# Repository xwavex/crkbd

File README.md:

# Singularity Keyboard, based on the Corne Keyboard.

## Parts
| Part | Amount | Description |
|:-|:-|:-|
| PCB | 2 | |
| Plate | 2 | |
| ProMicro | 2 | https://www.makershop.de/plattformen/arduino/pro-micro-32u4/ |
| TRRS Jack | 2 | MJ-4PP-9, PJ320A (3.5mm jack) |
| TRS(3-Pol) Cable | 1 | TRRS(4-Pol) Cable may be used as well? |
| Tactile Reset Switch | 2 | |
| Diode 1n4148w (sod 123) | 56 | For Low-Pro only surface mountable |
| Keyswitch | 56 | |
| Keycap | 56 | 54 x 1u and 2 x 1.5u |
| Standoffs / Spacer M2 | 14 | 6 mm for High-Pro, 4mm for Low-Pro |
| Standoffs / Spacer M2 8 mm or 10 mm | 4 | For OLED height |
| Screws M2 | 36 | 3 mm and 5 mm ? |
| Rubber feets | 8-10 | |

| Part (optional) | Amount | Description |
|:-|:-|:-|
| OLED Display | 2 | |
| 4 Pin Header | 2 | For easier exchange of OLED |
| 4 Pin  Sockets | 2 | For easier exchange of OLED |
| SK6812MINI | 72 | Top-facing 28, Bottom-facing 8 |

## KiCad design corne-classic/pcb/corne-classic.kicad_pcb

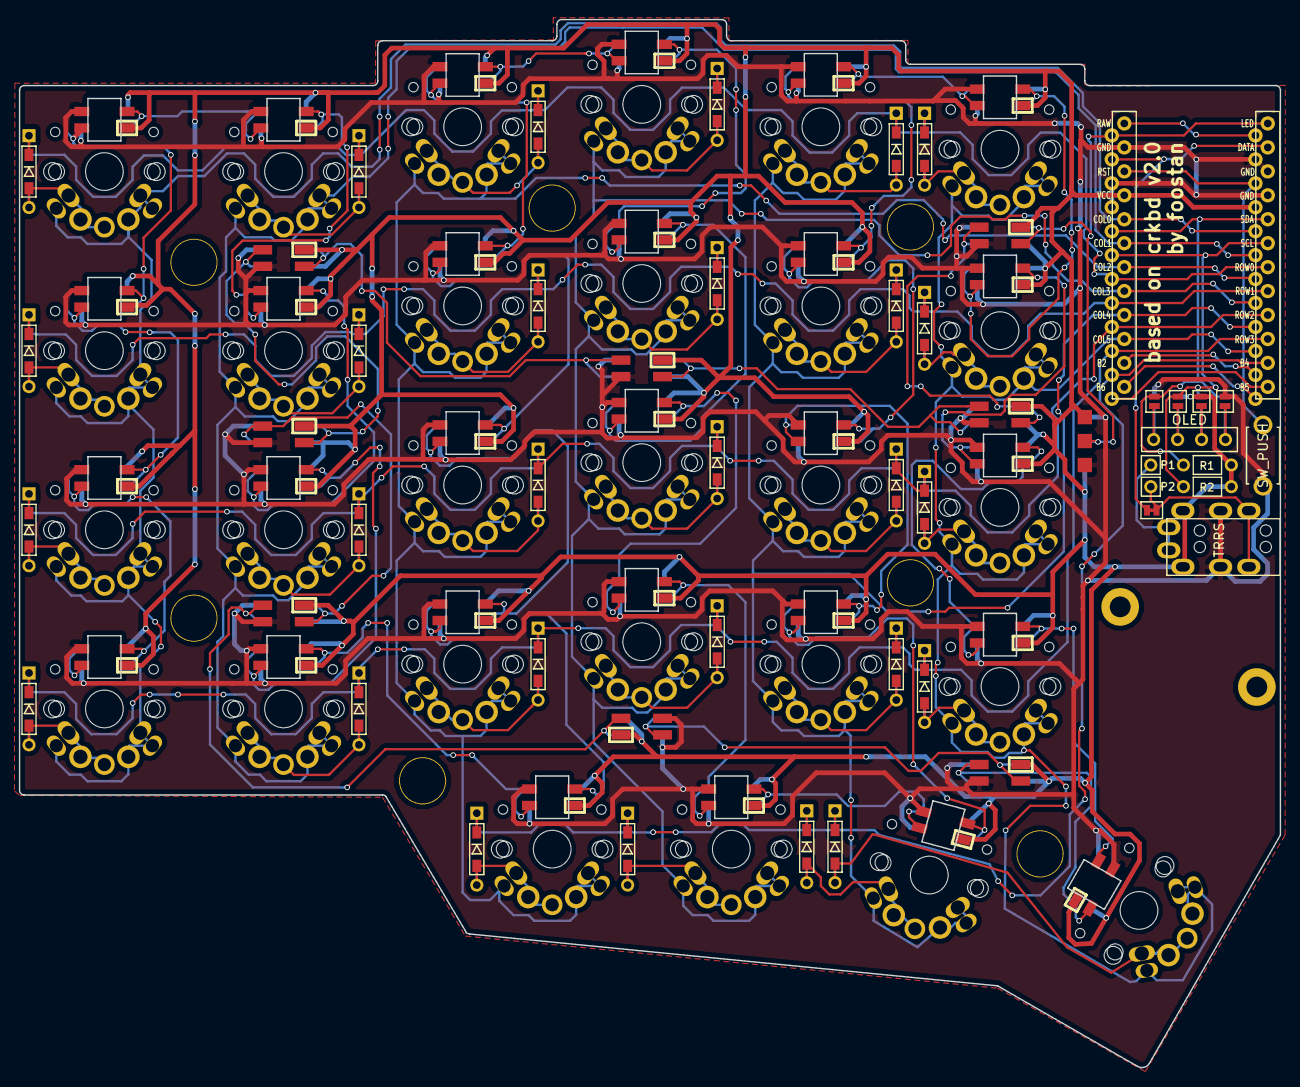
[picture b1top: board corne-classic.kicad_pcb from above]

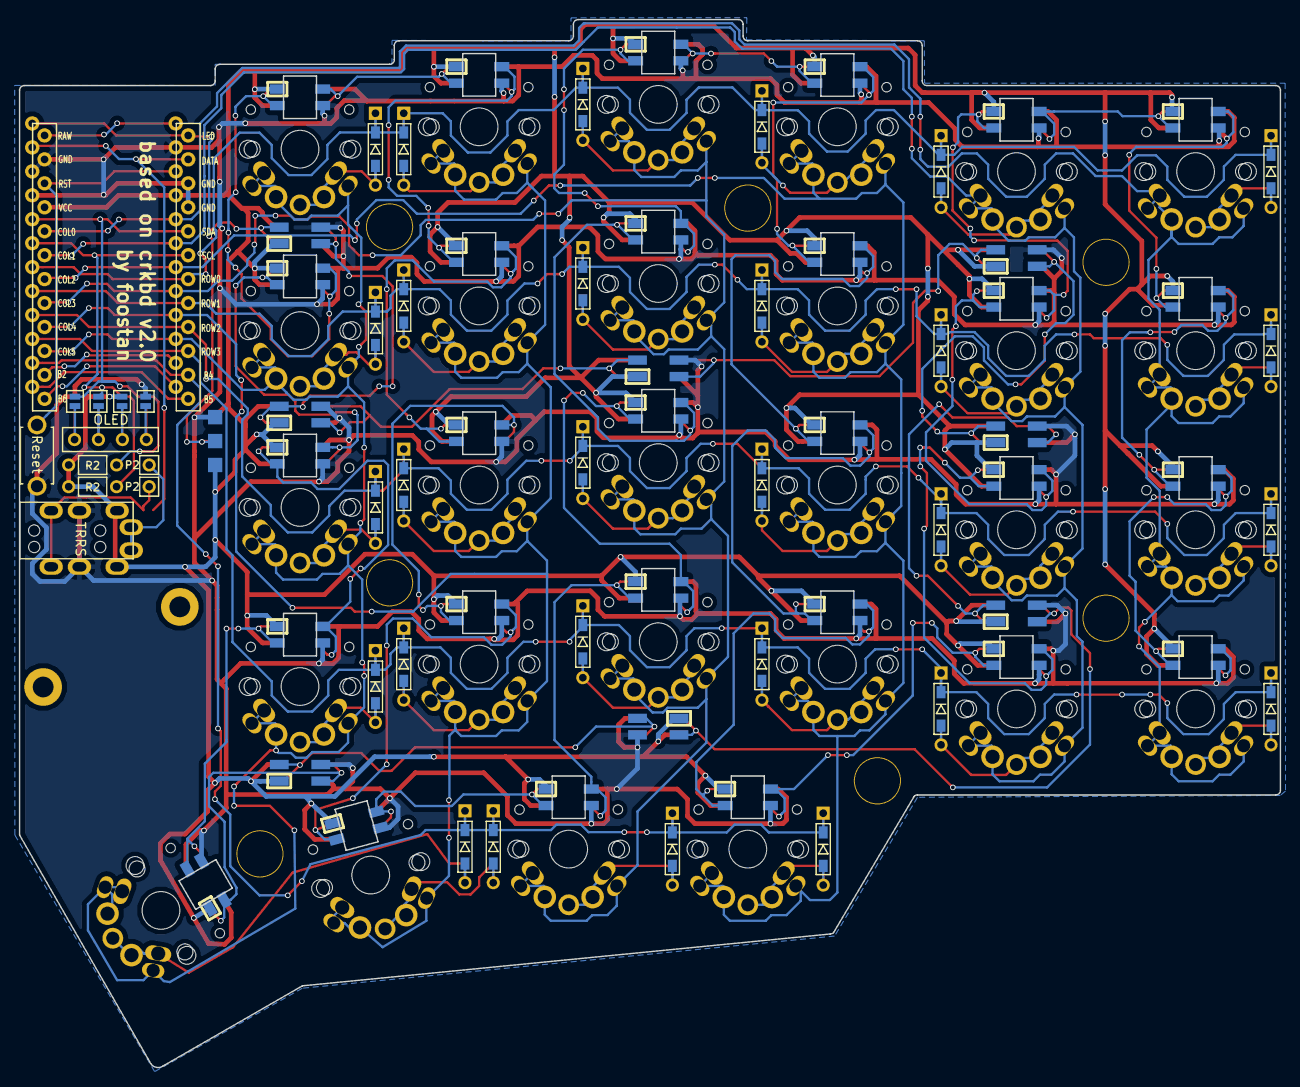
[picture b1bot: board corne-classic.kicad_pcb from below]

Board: 2 copper layers, 133.8 x 111.2 mm, 110 parts (4 on the bottom side), 87 nets.

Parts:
D1, D2, D3, D4, D5, D6, D7, D8, D9, D10, D11, D12, D13, D14, D15, D16, D17, D18, D19, D20, D21, D22, D23, D24, D25, D26, D27, D28: D; D3_TH_SMD
J1: MJ-4PP-9
J2: OLED
J3: LED; StripLED_rev
JP1: JPC2
JP2, JP3, JP4, JP5, JP6, JP7, JP8, JP9: Jumper
L0, L1, L2, L3, L4, L5, L6, L111: SK6812MINI; SK6812MINI_underglow_rev
L7, L8, L9, L10, L11, L12, L13, L14, L15, L16, L17, L18, L19, L20, L21, L22, L23, L24, L25, L26, L27, L28, L29, L30, L31, L32, L33, L34: SK6812MINI; SK6812MINI_rev
P1, P2: i2c-pin; 1pin_conn
R1, R2: R
RSW1: SW_PUSH; ResetSW
SW1, SW2, SW3, SW4, SW5, SW6, SW7, SW8, SW9, SW10, SW11, SW12, SW13, SW14, SW15, SW16, SW17, SW18, SW19, SW20, SW21, SW22, SW23, SW24, SW25, SW26, SW27: SW_PUSH; MX_ALPS_PG1350_noLed
SW28: SW_PUSH; MX_ALPS_PG1350_noLed_1.75u
U1: ProMicro; ProMicro_v2

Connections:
GND: J1.C, J3.1, JP2.1, JP9.1, L0.2, L1.2, L2.2, L3.2, L4.2, L5.2, L6.2, L7.2, L8.2, L9.2, L10.2, L11.2, L12.2, L13.2, L14.2, L15.2, L16.2, L17.2, L18.2, L19.2, L20.2, L21.2, L22.2, L23.2, L24.2, L25.2, L26.2, L27.2, L28.2, L29.2, L30.2, L31.2, L32.2, L33.2, L34.2, L111.2, RSW1.2, U1.3, U1.4, U1.23
LED: J3.2, L0.3, U1.1
unnamed: D1.2, SW1.2
unnamed: D2.2, SW2.2
unnamed: D3.2, SW3.2
unnamed: D4.2, SW4.2
unnamed: D5.2, SW5.2
unnamed: D6.2, SW6.2
unnamed: D7.2, SW7.2
unnamed: D8.2, SW8.2
unnamed: D9.2, SW9.2
unnamed: D10.2, SW10.2
unnamed: D11.2, SW11.2
unnamed: D12.2, SW12.2
unnamed: D13.2, SW13.2
unnamed: D14.2, SW14.2
unnamed: D15.2, SW15.2
unnamed: D16.2, SW16.2
unnamed: D17.2, SW17.2
unnamed: D18.2, SW18.2
unnamed: D19.2, SW19.2
unnamed: D20.2, SW20.2
unnamed: D21.2, SW21.2
unnamed: D22.2, SW22.2
unnamed: D23.2, SW23.2
unnamed: D24.2, SW24.2
unnamed: D25.2, SW25.2
unnamed: D26.2, SW26.2
unnamed: D27.2, SW27.2
unnamed: D28.2, SW28.2
unnamed: J1.A, P1.1
unnamed: J1.B, JP1.2, P2.1
unnamed: J2.1, JP5.2, JP9.2
unnamed: J2.2, JP4.2, JP8.2
unnamed: J2.3, JP3.2, JP7.2
unnamed: J2.4, JP2.2, JP6.2
unnamed: L0.1, L3.3
unnamed: L1.1, L4.3
unnamed: L1.3, L111.1
unnamed: L2.3, L3.1
unnamed: L4.1, L5.3
unnamed: L5.1, L6.3
unnamed: L7.3, L8.1
unnamed: L9.3, L10.1
unnamed: L10.3, L16.1
unnamed: L11.1, L17.3
unnamed: L11.3, L12.1
unnamed: L12.3, L18.1
unnamed: L13.1, L19.3
unnamed: L7.1, L13.3
unnamed: L8.3, L14.1
unnamed: L14.3, L20.1
unnamed: L15.1, L21.3
unnamed: L9.1, L15.3
unnamed: L16.3, L22.1
unnamed: L17.1, L23.3
unnamed: L18.3, L24.1
unnamed: L19.1, L25.3
unnamed: L20.3, L26.1
unnamed: L21.1, L27.3
unnamed: L22.3, L28.1
unnamed: L23.1, L29.3
unnamed: L24.3, L30.1
unnamed: L26.3, L31.1
unnamed: L27.1, L31.3
unnamed: L28.3, L32.1
unnamed: L29.1, L33.3
unnamed: L30.3, L34.1
unnamed: L32.3, L33.1
unnamed: L6.1, L34.3
unnamed: L2.1, L111.3
SCL: JP4.1, JP7.1, R2.2, U1.6
SDA: JP5.1, JP6.1, R1.2, U1.5
VCC: J1.D, J3.3, JP3.1, JP8.1, L0.4, L1.4, L2.4, L3.4, L4.4, L5.4, L6.4, L7.4, L8.4, L9.4, L10.4, L11.4, L12.4, L13.4, L14.4, L15.4, L16.4, L17.4, L18.4, L19.4, L20.4, L21.4, L22.4, L23.4, L24.4, L25.4, L26.4, L27.4, L28.4, L29.4, L30.4, L31.4, L32.4, L33.4, L34.4, L111.4, R1.1, R2.1, U1.21
col0: SW1.1, SW7.1, SW13.1, SW19.1, U1.20
col1: SW2.1, SW8.1, SW14.1, SW20.1, U1.19
col2: SW3.1, SW9.1, SW15.1, SW21.1, SW25.1, U1.18
col3: SW4.1, SW10.1, SW16.1, SW22.1, SW26.1, U1.17
col4: SW5.1, SW11.1, SW17.1, SW23.1, SW27.1, U1.16
col5: SW6.1, SW12.1, SW18.1, SW24.1, SW28.1, U1.15
data: JP1.1, U1.2
reset: RSW1.1, U1.22
row0: D1.1, D2.1, D3.1, D4.1, D5.1, D6.1, U1.7
row1: D7.1, D8.1, D9.1, D10.1, D11.1, D12.1, U1.8
row2: D13.1, D14.1, D15.1, D16.1, D17.1, D18.1, U1.9
row3: D19.1, D20.1, D21.1, D22.1, D23.1, D24.1, U1.10
row4: D25.1, D26.1, D27.1, D28.1, U1.11

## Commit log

2018-09-22 Add a thumb key
2018-10-13 new stuff
2018-10-29 fixed some connections
2018-10-30 further routing fixes
2018-10-30 routing
2018-11-02 started to change the footprint to fit mill max inside
2018-11-02 rerouting
2018-11-05 added text
2018-11-07 thumb button update
2018-11-08 logo added
2018-11-08 restructuring
2018-11-11 final?
2018-11-12 included all gerber files
